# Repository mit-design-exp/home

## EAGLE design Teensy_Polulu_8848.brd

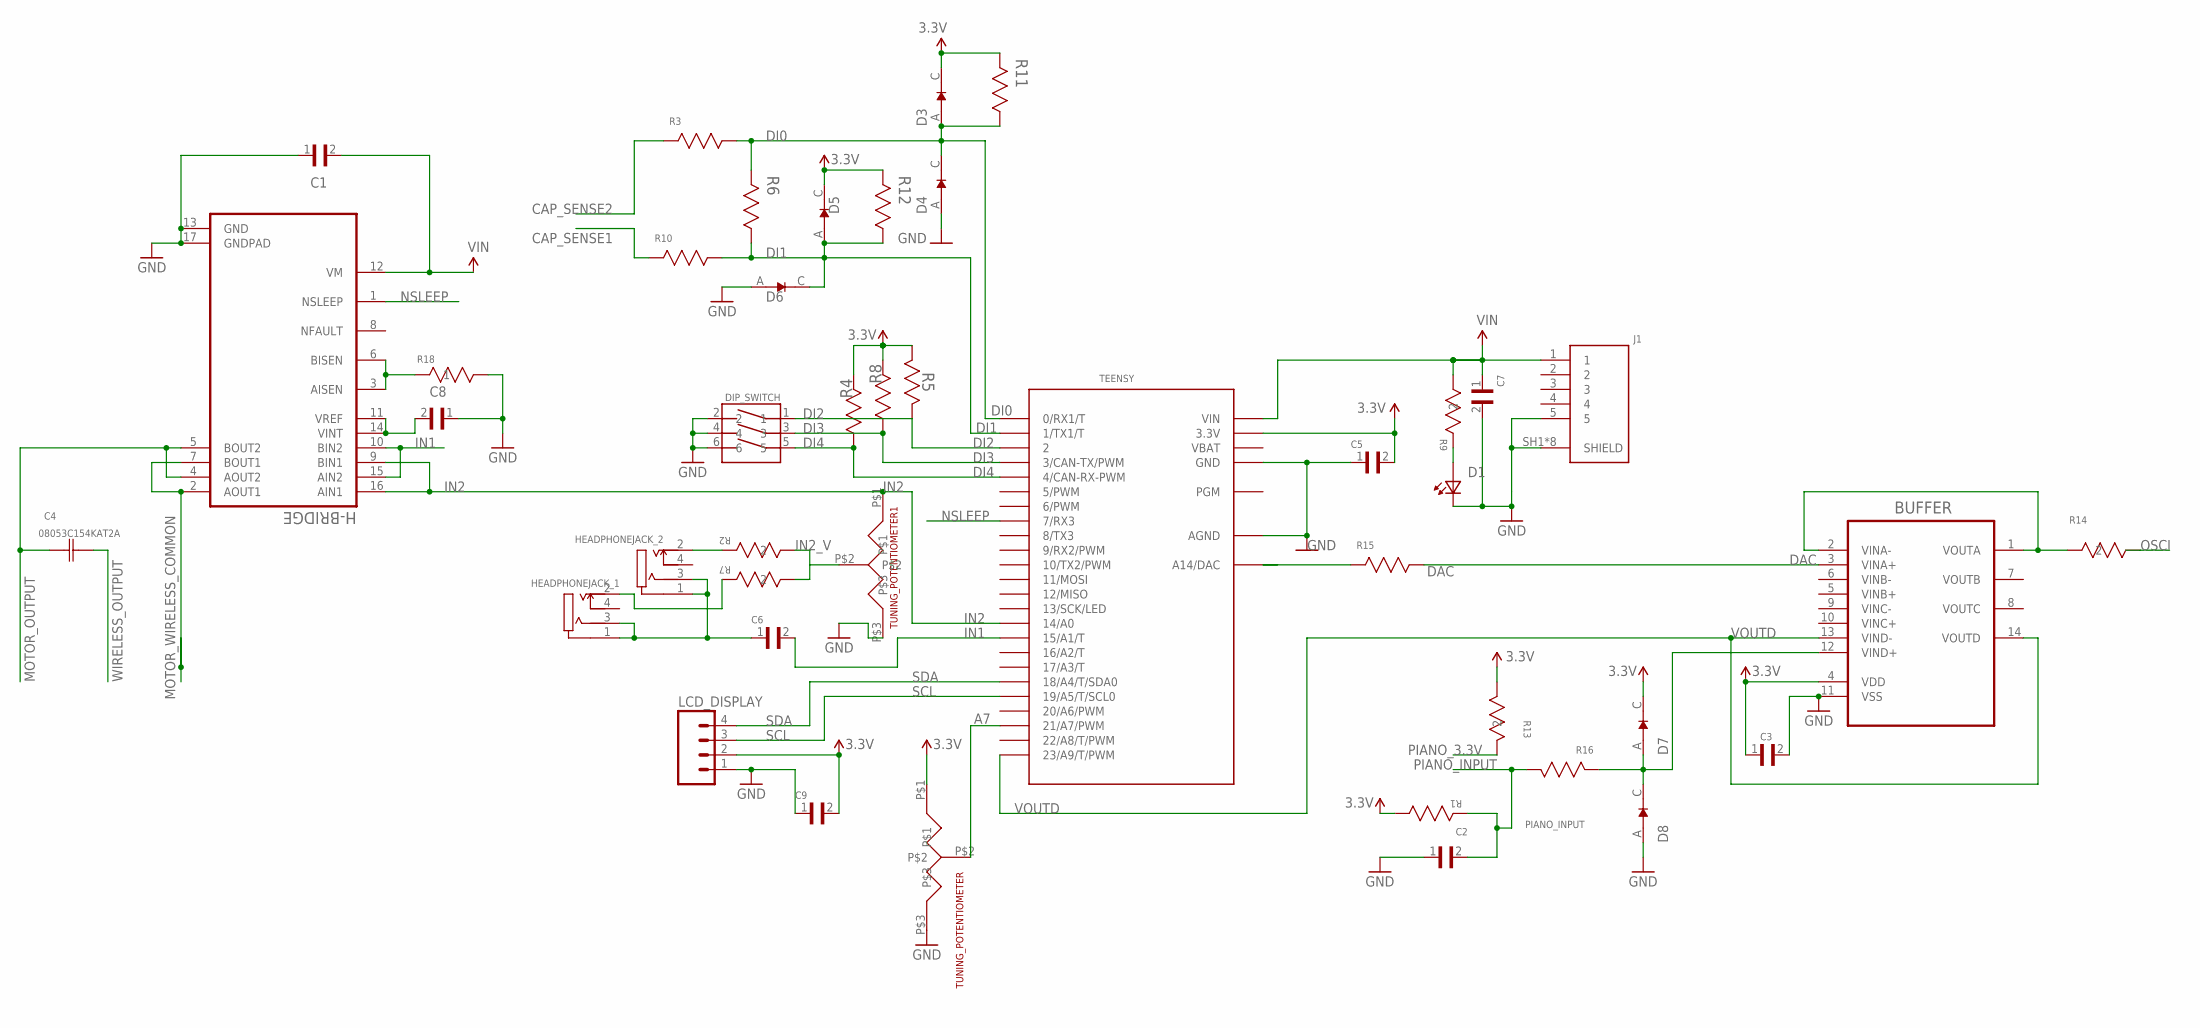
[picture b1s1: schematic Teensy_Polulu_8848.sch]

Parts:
BUFFER: MCP6024-I/SL; SOIC127P600X175-14N
C1, C3, C5, C6, C7, C9: GRM219R60J476ME44D; CAPC2012X135N
C2: C2012C0G1V303J060AC; INDC2012X87N
C4: 08053C154KAT2A; CAPC2013X94N
C8: GRM21BR60J225KA01L; CAPC2012X135N
D1: TLMY1100-GS08; 0603
D3, D4, D5, D6, D7, D8: 1N4148W-7-F; SOD3715X135N
DIP_SWITCH: SDA03H1SBD; SW_SDA03H1SBD
H-BRIDGE: DRV8848PWP; SOP65P640X120-17N
HEADPHONEJACK_1, HEADPHONEJACK_2: 47257-0001; MOLEX_47257-0001
J1: 1050170001; MOLEX_1050170001
LCD_DISPLAY: M04POLAR; MOLEX-1X4
R1, R6, R11, R12: RT0805FRE071ML; RESC2013X65N
R2, R7: RT0805FRE07100RL; RC0805N
R3, R4, R5, R8, R10, R15, R16: RT0805FRE0710KL; RESC2013X65N
R9, R14: RT0805FRE071KL; RC0805N
R13: RT0805BRD0749R9L; RC0805N
R18: CSRN2512FKR250; STA_CSRN2512
TEENSY: TEENSY_3.1-3.2_OUTER_ROW; TEENSY_3.0-3.2&LC_OUTER_ROW
TUNING_POTENTIOMETER, TUNING_POTENTIOMETER1: POT_PTV09A-4225F-B102-ND

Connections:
3.3V: BUFFER.4 (VDD), C3.1, C5.2, C9.2, D3.C (K), D5.C (K), D7.C (K), LCD_DISPLAY.2, R1.1 (R1), R4.1 (R1), R5.1 (R1), R8.1 (R1), R11.2 (R2), R12.2 (R2), R13.1, TEENSY.3.3V, TEENSY.3.3V1 (3.3V), TUNING_POTENTIOMETER.P$1
A7: TEENSY.21/A7 (21/A7/PWM), TUNING_POTENTIOMETER.P$2
CAP_SENSE1: R10.2 (R2)
CAP_SENSE2: R3.2 (R2)
DAC: BUFFER.3 (VINA+), R15.1 (R1)
DI0: D3.A, D4.C (K), R3.1 (R1), R6.2 (R2), R11.1 (R1), TEENSY.0 (0/RX1/T)
DI1: D5.A, D6.C (K), R6.1 (R1), R10.1 (R1), R12.1 (R1), TEENSY.1 (1/TX1/T)
DI2: DIP_SWITCH.1, R5.2 (R2), TEENSY.2
DI3: DIP_SWITCH.3, R8.2 (R2), TEENSY.3 (3/CAN-TX/PWM)
DI4: DIP_SWITCH.5, R4.2 (R2), TEENSY.4 (4/CAN-RX-PWM)
GND: BUFFER.11 (VSS), C1.1, C2.1, C3.2, C5.1, C7.2, C8.1, C9.1, D1.1 (K2), D4.A, D6.A, D8.A, DIP_SWITCH.2, DIP_SWITCH.4, DIP_SWITCH.6, H-BRIDGE.13 (GND), H-BRIDGE.17 (GNDPAD), J1.5, J1.SH1 (SHIELD), J1.SH2 (SHIELD), J1.SH3 (SHIELD), J1.SH4 (SHIELD), J1.SH5 (SHIELD), J1.SH6 (SHIELD), J1.SH7 (SHIELD), J1.SH8 (SHIELD), LCD_DISPLAY.1, R18.2, TEENSY.AGND, TEENSY.GND, TEENSY.GND1 (GND), TUNING_POTENTIOMETER.P$3, TUNING_POTENTIOMETER1.P$3
IN1: C6.2, H-BRIDGE.10 (BIN2), H-BRIDGE.15 (AIN2), TEENSY.15/A1 (15/A1/T)
IN2: H-BRIDGE.9 (BIN1), H-BRIDGE.16 (AIN1), TEENSY.14/A0, TUNING_POTENTIOMETER1.P$1
IN2_V: R2.2, R7.2, TUNING_POTENTIOMETER1.P$2
MOTOR_OUTPUT: C4.1 (C1), H-BRIDGE.4 (AOUT2), H-BRIDGE.5 (BOUT2)
MOTOR_WIRELESS_COMMON: H-BRIDGE.2 (AOUT1), H-BRIDGE.7 (BOUT1)
unnamed: HEADPHONEJACK_2.2, R2.1
unnamed: D1.2 (A2), R9.1
unnamed: HEADPHONEJACK_1.2, R7.1
unnamed: H-BRIDGE.3 (AISEN), H-BRIDGE.6 (BISEN), R18.1
unnamed: C8.2, H-BRIDGE.11 (VREF), H-BRIDGE.14 (VINT)
unnamed: C6.1, HEADPHONEJACK_1.1, HEADPHONEJACK_1.3, HEADPHONEJACK_2.1, HEADPHONEJACK_2.3
unnamed: BUFFER.1 (VOUTA), BUFFER.2 (VINA-), R14.2
unnamed: BUFFER.12 (VIND+), D7.A, D8.C (K), R16.2 (R2)
unnamed: R15.2 (R2), TEENSY.RESET/DAC (A14/DAC)
NSLEEP: H-BRIDGE.1 (NSLEEP), TEENSY.7 (7/RX3)
OSCI: R14.1
PIANO_3.3V: R13.2
PIANO_INPUT: C2.2, R1.2 (R2), R16.1 (R1)
SCL: LCD_DISPLAY.3, TEENSY.19/A5 (19/A5/T/SCL0)
SDA: LCD_DISPLAY.4, TEENSY.18/A4 (18/A4/T/SDA0)
VBAT: TEENSY.VBAT
VIN: C1.2, C7.1, H-BRIDGE.12 (VM), J1.1, R9.2, TEENSY.VIN
VOUTD: BUFFER.13 (VIND-), BUFFER.14 (VOUTD), TEENSY.23/A9 (23/A9/T/PWM)
WIRELESS_OUTPUT: C4.2 (C2)

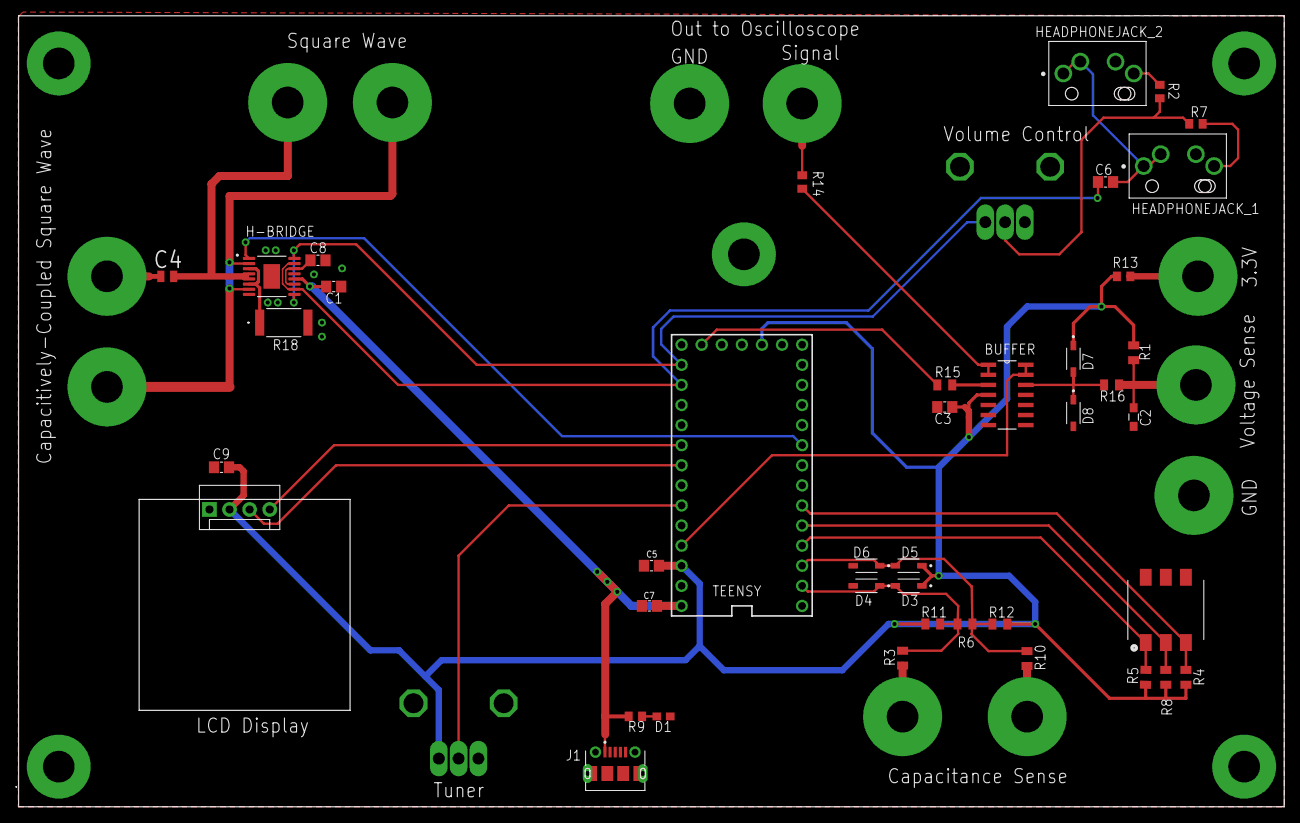
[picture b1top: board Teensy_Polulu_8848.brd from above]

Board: 2 copper layers, 160.3 x 100.0 mm, 43 parts (0 on the bottom side), 29 nets.

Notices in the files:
parts and their libraries:
SparkFun-Connectors: Licensing: Creative Commons ShareAlike 4.0 International - https://creativecommons.org/licenses/by-sa/4.0
